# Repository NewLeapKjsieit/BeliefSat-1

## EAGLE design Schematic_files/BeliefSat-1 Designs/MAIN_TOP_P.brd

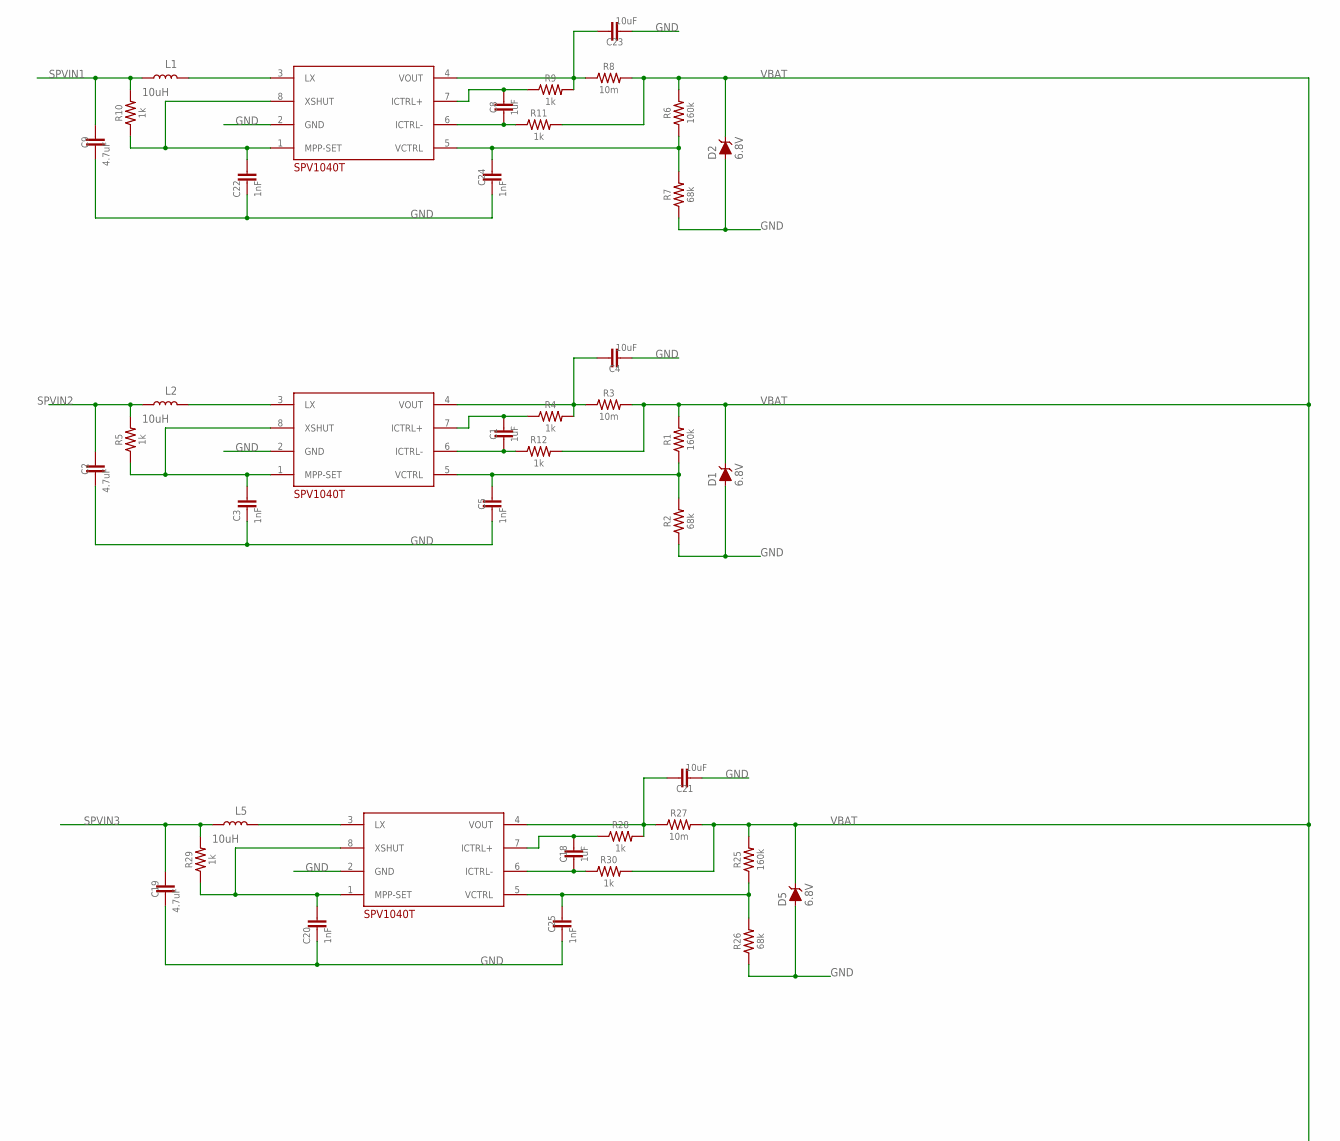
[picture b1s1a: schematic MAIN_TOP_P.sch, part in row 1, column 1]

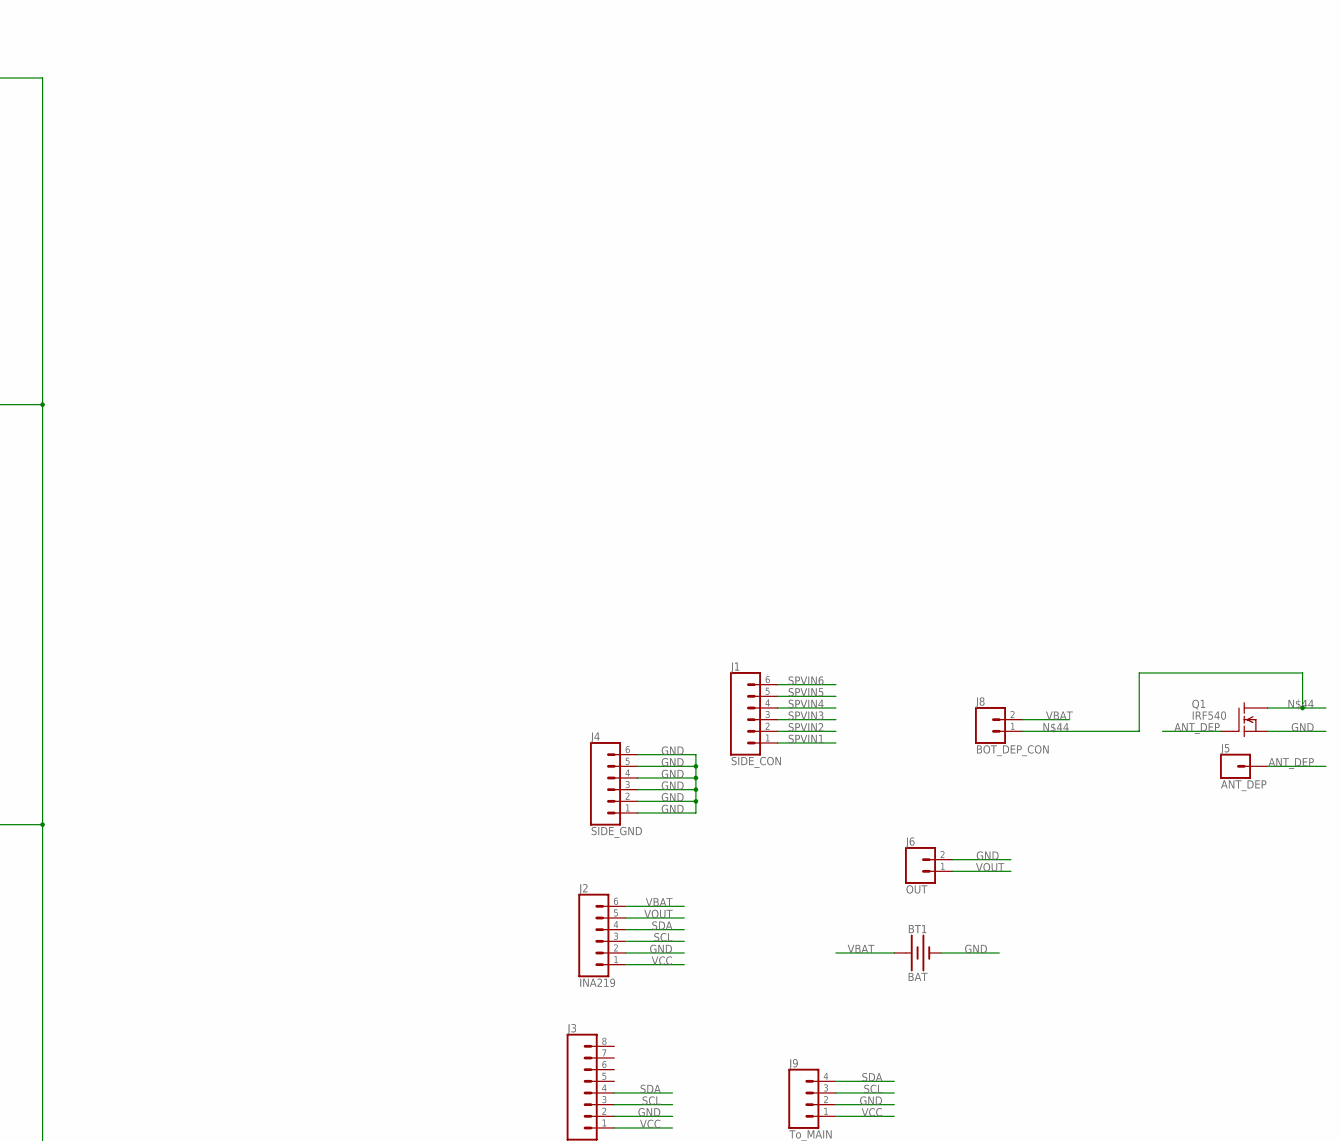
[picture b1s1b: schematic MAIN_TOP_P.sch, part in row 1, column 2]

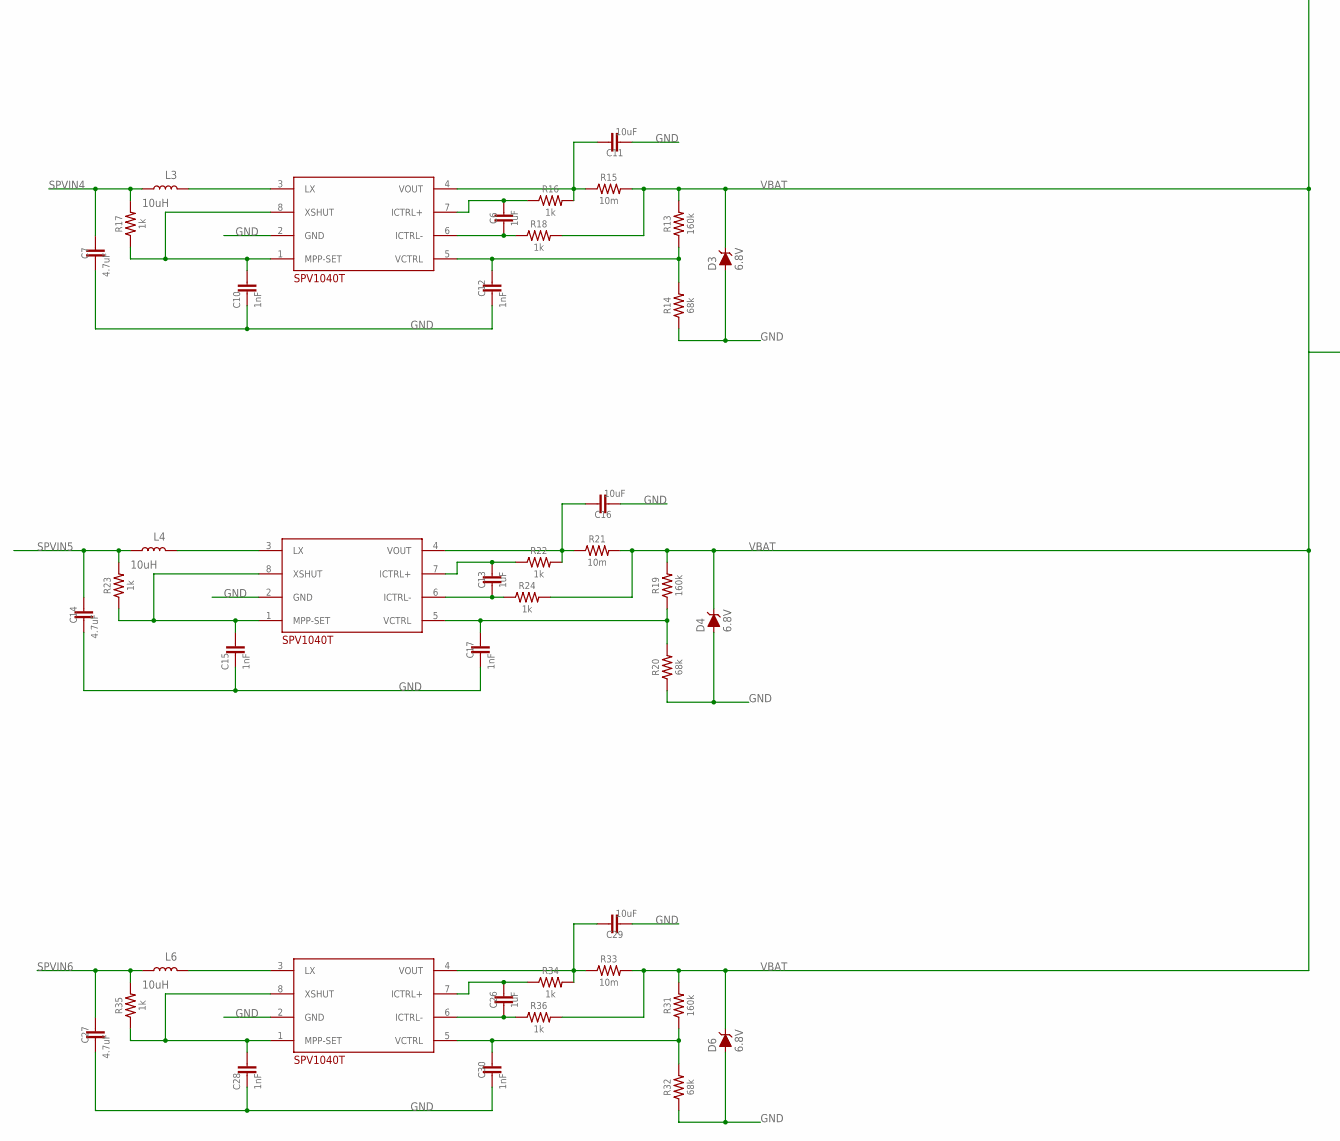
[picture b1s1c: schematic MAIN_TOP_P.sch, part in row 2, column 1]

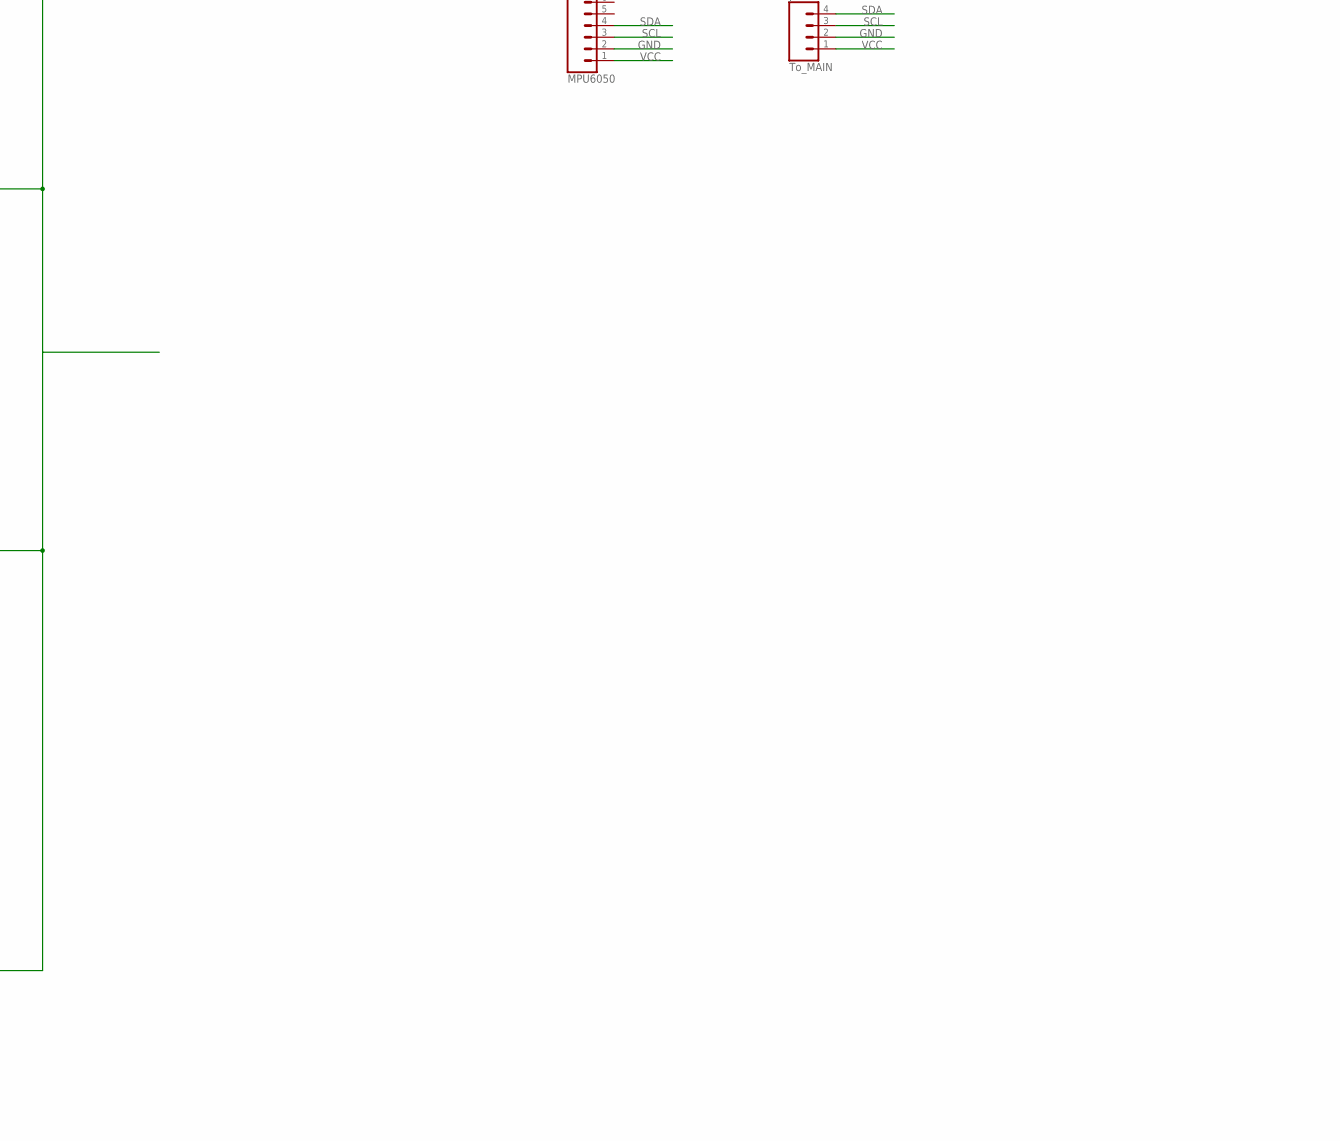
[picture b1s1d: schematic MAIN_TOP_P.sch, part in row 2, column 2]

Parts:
BT1: BAT; BATTERY_18650-HOLDER
C1, C6, C8, C13, C18, C26: 1uF; 0603
C2, C7, C9, C14, C19, C27: 4.7uF; 0603
C3, C5, C10, C12, C15, C17, C20, C22, C24, C25, C28, C30: 1nF; 0603
C4, C11, C16, C21, C23, C29: 10uF; 0603
D1, D2, D3, D4, D5, D6: 6.8V; SOD-323
J1: SIDE_CON; 1X06
J2: INA219; 1X06
J3: MPU6050; 1X08
J4: SIDE_GND; 1X06
J5: ANT_DEP; 1X01
J6: OUT; 1X02
J8: BOT_DEP_CON; 1X02
J9: To_MAIN; 1X04
L1, L2, L3, L4, L5, L6: 10uH; 0603
Q1: IRF540; TO220
R1, R6, R13, R19, R25, R31: 160k; RES_0603
R2, R7, R14, R20, R26, R32: 68k; RES_0603
R3, R8, R15, R21, R27, R33: 10m; RES_0603
R4, R5, R9, R10, R11, R12, R16, R17, R18, R22, R23, R24, R28, R29, R30, R34, R35, R36: 1k; RES_0603
SPV_1, SPV_2, SPV_3, SPV_4, SPV_5, SPV_6: SPV1040T_; SOP65P640X120-8N

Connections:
ANT_DEP: J5.1, Q1.1 (G)
GND: BT1.GND@1 (-), C2.2, C3.2, C4.2, C5.2, C7.2, C9.2, C10.2, C11.2, C12.2, C14.2, C15.2, C16.2, C17.2, C19.2, C20.2, C21.2, C22.2, C23.2, C24.2, C25.2, C27.2, C28.2, C29.2, C30.2, D1.A, D2.A, D3.A, D4.A, D5.A, D6.A, J2.2, J3.2, J4.1, J4.2, J4.3, J4.4, J4.5, J4.6, J6.2, J9.2, Q1.3 (S), R2.1, R7.1, R14.1, R20.1, R26.1, R32.1, SPV_1.2 (GND), SPV_2.2 (GND), SPV_3.2 (GND), SPV_4.2 (GND), SPV_5.2 (GND), SPV_6.2 (GND)
unnamed: L2.2, SPV_2.3 (LX)
unnamed: C3.1, R5.1, SPV_2.1 (MPP-SET), SPV_2.8 (XSHUT)
unnamed: C5.1, R1.1, R2.2, SPV_2.5 (VCTRL)
unnamed: C1.2, R12.1, SPV_2.6 (ICTRL-)
unnamed: L1.2, SPV_1.3 (LX)
unnamed: C1.1, R4.1, SPV_2.7 (ICTRL+)
unnamed: C4.1, R3.1, R4.2, SPV_2.4 (VOUT)
unnamed: L3.2, SPV_4.3 (LX)
unnamed: C10.1, R17.1, SPV_4.1 (MPP-SET), SPV_4.8 (XSHUT)
unnamed: C12.1, R13.1, R14.2, SPV_4.5 (VCTRL)
unnamed: C6.2, R18.1, SPV_4.6 (ICTRL-)
unnamed: C6.1, R16.1, SPV_4.7 (ICTRL+)
unnamed: C11.1, R15.1, R16.2, SPV_4.4 (VOUT)
unnamed: L4.2, SPV_5.3 (LX)
unnamed: C15.1, R23.1, SPV_5.1 (MPP-SET), SPV_5.8 (XSHUT)
unnamed: C17.1, R19.1, R20.2, SPV_5.5 (VCTRL)
unnamed: C13.2, R24.1, SPV_5.6 (ICTRL-)
unnamed: C13.1, R22.1, SPV_5.7 (ICTRL+)
unnamed: C16.1, R21.1, R22.2, SPV_5.4 (VOUT)
unnamed: L5.2, SPV_3.3 (LX)
unnamed: C20.1, R29.1, SPV_3.1 (MPP-SET), SPV_3.8 (XSHUT)
unnamed: C25.1, R25.1, R26.2, SPV_3.5 (VCTRL)
unnamed: C18.2, R30.1, SPV_3.6 (ICTRL-)
unnamed: C18.1, R28.1, SPV_3.7 (ICTRL+)
unnamed: C21.1, R27.1, R28.2, SPV_3.4 (VOUT)
unnamed: L6.2, SPV_6.3 (LX)
unnamed: C28.1, R35.1, SPV_6.1 (MPP-SET), SPV_6.8 (XSHUT)
unnamed: C30.1, R31.1, R32.2, SPV_6.5 (VCTRL)
unnamed: C26.2, R36.1, SPV_6.6 (ICTRL-)
unnamed: C26.1, R34.1, SPV_6.7 (ICTRL+)
unnamed: C22.1, R10.1, SPV_1.1 (MPP-SET), SPV_1.8 (XSHUT)
unnamed: C24.1, R6.1, R7.2, SPV_1.5 (VCTRL)
unnamed: C29.1, R33.1, R34.2, SPV_6.4 (VOUT)
unnamed: C8.2, R11.1, SPV_1.6 (ICTRL-)
unnamed: C8.1, R9.1, SPV_1.7 (ICTRL+)
unnamed: C23.1, R8.1, R9.2, SPV_1.4 (VOUT)
unnamed: J8.1, Q1.2 (D)
SCL: J2.3, J3.3, J9.3
SDA: J2.4, J3.4, J9.4
SPVIN1: C9.1, J1.1, L1.1, R10.2
SPVIN2: C2.1, J1.2, L2.1, R5.2
SPVIN3: C19.1, J1.3, L5.1, R29.2
SPVIN4: C7.1, J1.4, L3.1, R17.2
SPVIN5: C14.1, J1.5, L4.1, R23.2
SPVIN6: C27.1, J1.6, L6.1, R35.2
VBAT: BT1.PWR@1 (+), D1.C, D2.C, D3.C, D4.C, D5.C, D6.C, J2.6, J8.2, R1.2, R3.2, R6.2, R8.2, R11.2, R12.2, R13.2, R15.2, R18.2, R19.2, R21.2, R24.2, R25.2, R27.2, R30.2, R31.2, R33.2, R36.2
VCC: J2.1, J3.1, J9.1
VOUT: J2.5, J6.1

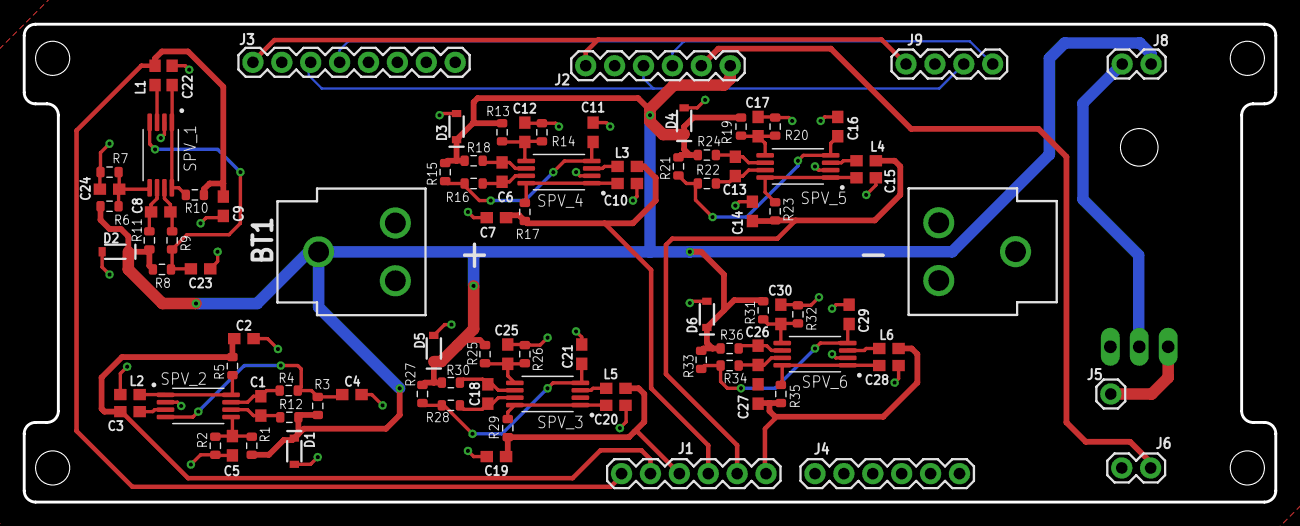
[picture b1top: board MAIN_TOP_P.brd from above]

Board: 2 copper layers, 110.0 x 42.0 mm, 94 parts (1 on the bottom side), 50 nets.

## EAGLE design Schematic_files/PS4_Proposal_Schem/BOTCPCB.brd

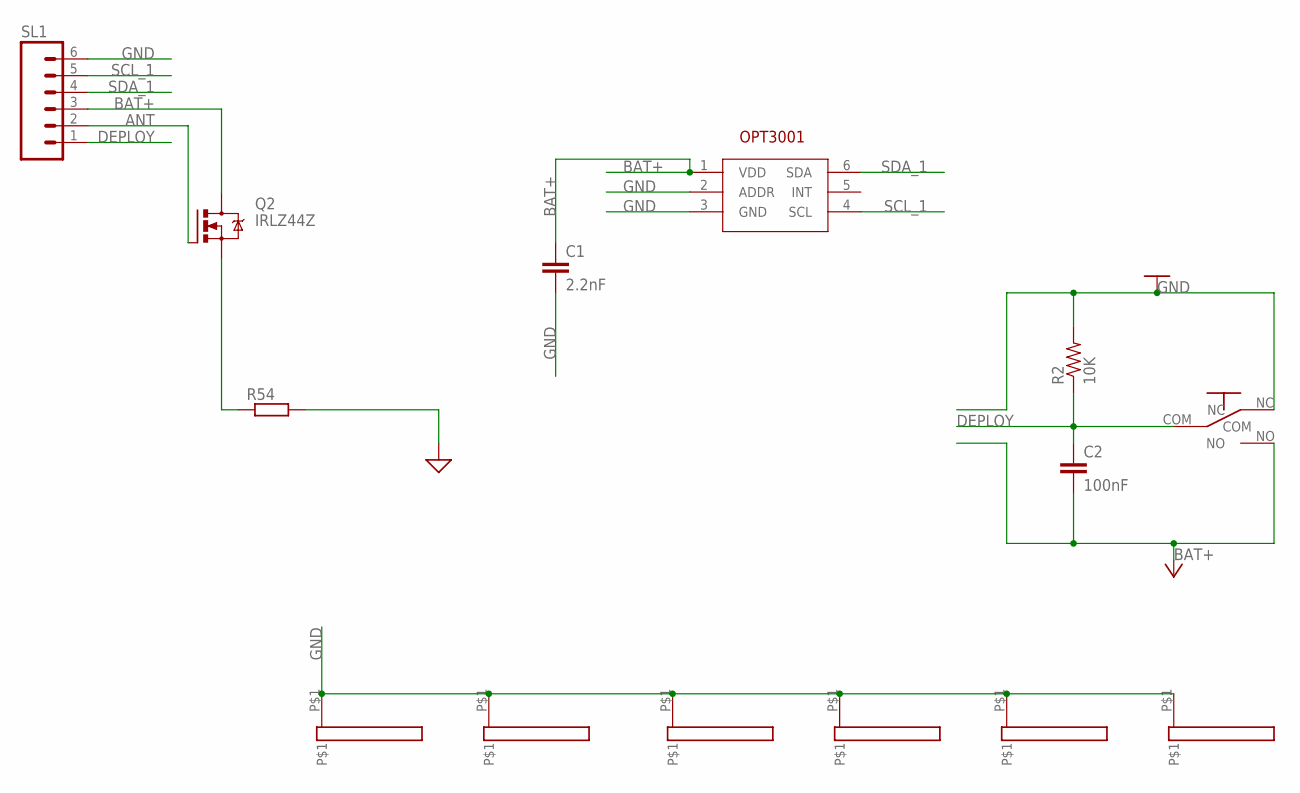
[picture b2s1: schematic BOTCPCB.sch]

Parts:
C1: 2.2nF; 0603
C2: 100nF; 0805
Q2: IRLZ44Z; TO220BH
R2: 10K; 0805
R54: R-EU_0204/2V; 0204V
SL1: M06; 06P
U1: SON65P200X200X65-7N
U$1, U$2, U$4, U$5, U$7, U$8: 16X2
U$6: OMRON-D2FA; OMRON-D2F-A

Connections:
ANT: Q2.G, SL1.2
BAT+: C1.1, C2.2, Q2.D, SL1.3, U1.1 (VDD), U$6.NO
DEPLOY: C2.1, R2.1, SL1.1, U$6.COM
GND: C1.2, R2.2, R54.2, SL1.6, U1.2 (ADDR), U1.3 (GND), U$1.P$1, U$2.P$1, U$4.P$1, U$5.P$1, U$6.NC, U$7.P$1, U$8.P$1
unnamed: Q2.S, R54.1
SCL_1: SL1.5, U1.4 (SCL)
SDA_1: SL1.4, U1.6 (SDA)

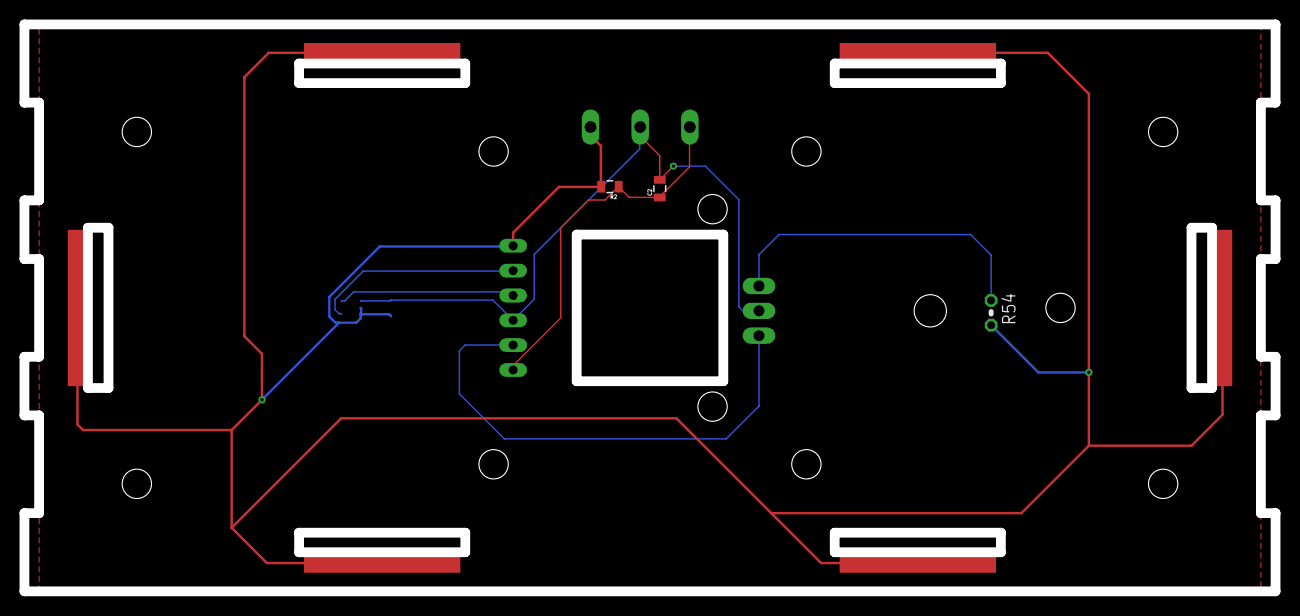
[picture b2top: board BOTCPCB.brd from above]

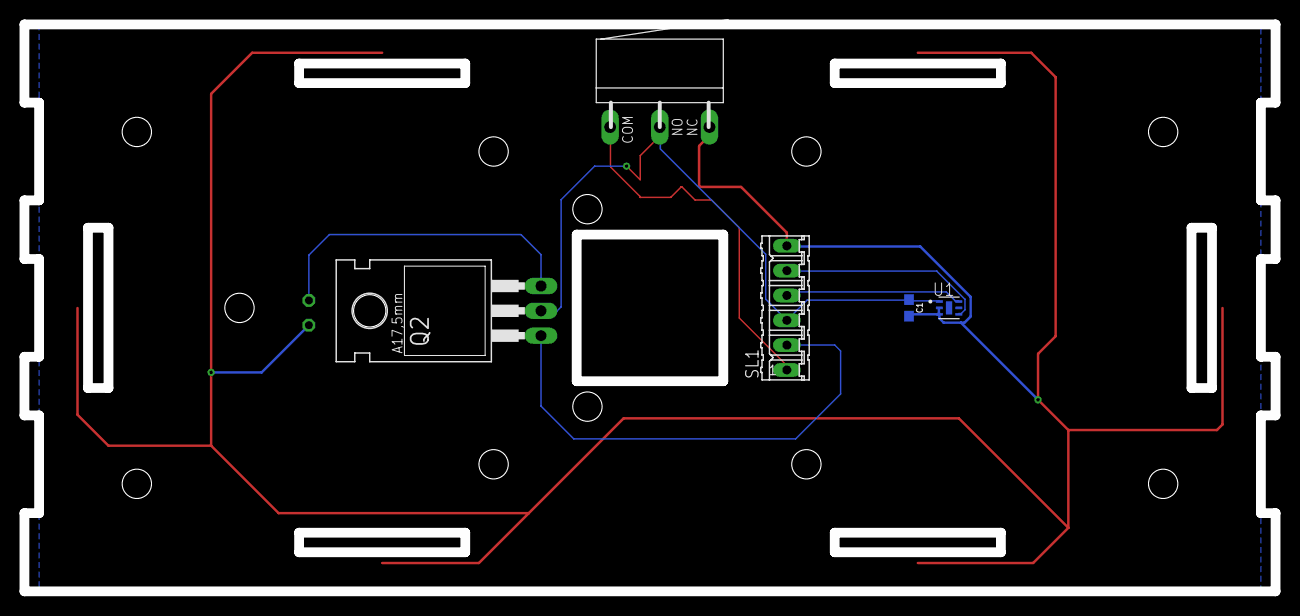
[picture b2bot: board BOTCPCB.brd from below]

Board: 2 copper layers, 128.0 x 58.0 mm, 14 parts (5 on the bottom side), 7 nets.

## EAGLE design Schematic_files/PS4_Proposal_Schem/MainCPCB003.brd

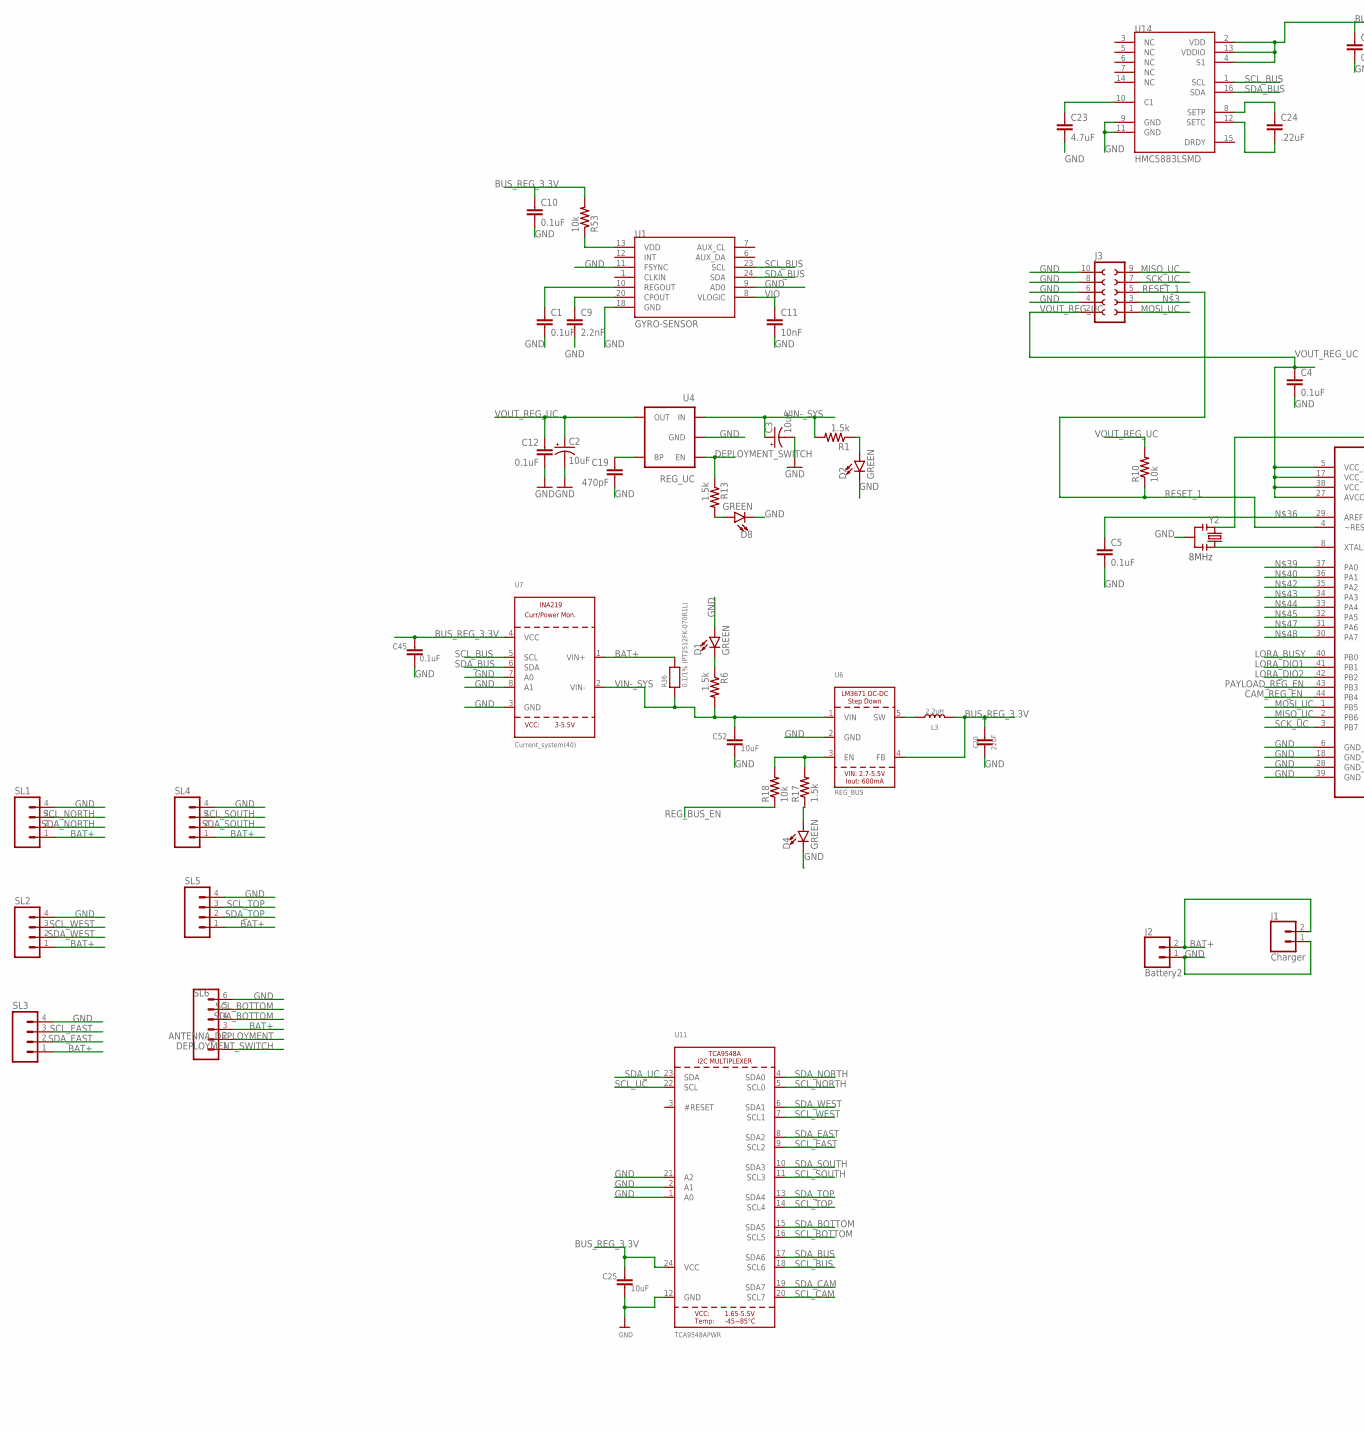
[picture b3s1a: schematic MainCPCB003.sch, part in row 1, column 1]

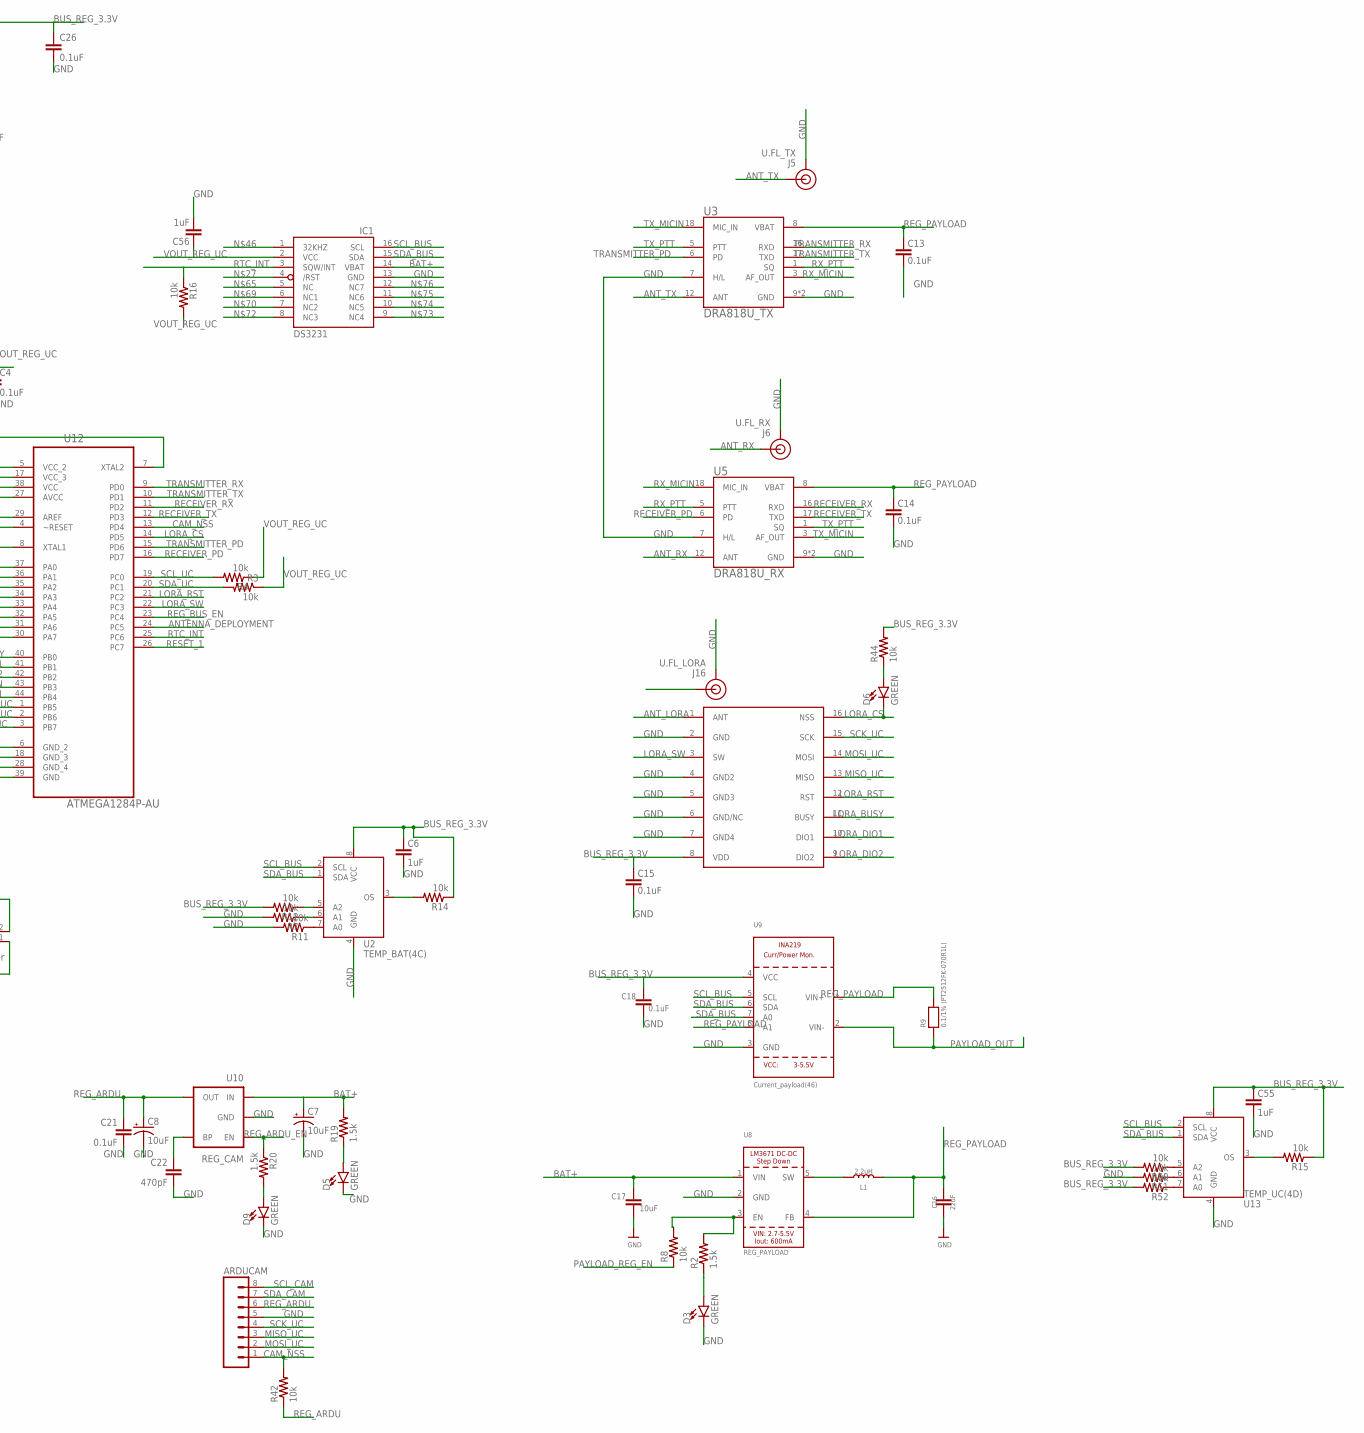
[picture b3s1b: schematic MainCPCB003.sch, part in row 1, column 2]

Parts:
ARDUCAM: M08; 08P
C1, C4, C5, C10, C12, C13, C14, C15, C21: 0.1uF; 0603-CAP
C2, C3, C7, C8: 10uF; 0603-POLAR
C6, C55, C56: 1uF; 0603-CAP
C9: 2.2nF; 0603-CAP
C11: 10nF; 0603-CAP
C16, C20: 22uF; 0603
C17, C25, C52: 10uF; 0603
C18, C26, C45: 0.1uF; 0603
C19, C22: 470pF; 0603-CAP
C23: 4.7uF; 0603
C24: .22uF; 0603
D1, D2, D3, D4, D5, D6, D8, D9: GREEN; LED-0603
IC1: DS3231/SO; SO16W
J1: Charger; 1X02
J2: Battery2; 1X02
J3: SOCKET-10V; S10V
J5: U.FL_TX; U.FL
J6: U.FL_RX; U.FL
J16: U.FL_LORA; U.FL
L1, L3: 2.2uH; 0603
R1, R2, R6, R13, R17, R19, R20: 1.5k; 0603-RES
R3, R4, R7, R11, R12, R14, R15, R16, R18, R42, R44, R50, R51, R52, R53: 10k; 0603-RES
R8, R10: 10k; 0402-RES
R9, R36: 0.1/1% (PT2512FK-070R1L); 2512
SL1, SL2, SL3, SL4, SL5: M04; 04P
SL6: M06; 06P
U1: GYRO-SENSOR; QFN-24-4MM2
U2: TEMP_BAT(4C); SOT505-1
U3: DRA818U_TX; DORJI_DRA818U
U4: REG_UC; SOT23-5
U5: DRA818U_RX; DORJI_DRA818U
U6: REG_BUS; SOT23-5
U7: Current_system(40); SOT23-8
U8: REG_PAYLOAD; SOT23-5
U9: Current_payload(46); SOT23-8
U10: REG_CAM; SOT23-5
U11: TCA9548APWR; TSSOP24
U12: ATMEGA1284P-AU; QFP80P1200X1200X120-44N
U13: TEMP_UC(4D); SOT505-1
U14: HMC5883LSMD; 16LPCC
U$1: DRF1268; RESCAV180P1570X1400X300-16
Y2: RESONATORSMD; RESONATOR-SMD

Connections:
ANTENNA_DEPLOYMENT: SL6.2, U12.24 (PC5)
ANT_LORA: J16.FEED (SIGNAL), U$1.1 (ANT)
ANT_RX: J6.FEED (SIGNAL), U5.12 (ANT)
ANT_TX: J5.FEED (SIGNAL), U3.12 (ANT)
BAT+: C7.+, C17.1, IC1.14 (VBAT), J1.2, J2.2, R19.2, R36.2, SL1.1, SL2.1, SL3.1, SL4.1, SL5.1, SL6.3, U7.1 (VIN+), U8.1 (VIN), U10.1 (IN)
BUS_REG_3.3V: C6.2, C10.1, C15.2, C18.1, C20.1, C25.1, C26.1, C45.1, C55.2, L3.2, R12.2, R14.1, R15.1, R44.2, R50.2, R52.2, R53.2, U2.8 (VCC), U6.4 (FB), U7.4 (VCC), U9.4 (VCC), U11.24 (VCC), U13.8 (VCC), U14.2 (VDD), U14.4 (S1), U14.13 (VDDIO), U$1.8 (VDD)
CAM_NSS: ARDUCAM.1, R42.2, U12.13 (PD4)
CAM_REG_EN: U12.44 (PB4)
DEPLOYMENT_SWITCH: R13.1, SL6.1, U4.3 (EN)
GND: ARDUCAM.5, C1.2, C2.-, C3.-, C4.2, C5.2, C6.1, C7.-, C8.-, C9.2, C10.2, C11.2, C12.2, C13.1, C14.1, C15.1, C16.2, C17.2, C18.2, C19.2, C20.2, C21.2, C22.2, C23.2, C25.2, C26.2, C45.2, C52.2, C55.1, C56.1, D1.A, D2.C, D3.C, D4.C, D5.C, D8.C, D9.C, IC1.13 (GND), J1.1, J2.1, J3.4, J3.6, J3.8, J3.10, J5.1 (GND), J5.2 (GND), J6.1 (GND), J6.2 (GND), J16.1 (GND), J16.2 (GND), R7.2, R11.2, R51.2, SL1.4, SL2.4, SL3.4, SL4.4, SL5.4, SL6.6, U1.9 (AD0), U1.11 (FSYNC), U1.18 (GND), U2.4 (GND), U3.7 (H/L), U3.9 (GND), U3.10 (GND), U4.2 (GND), U5.7 (H/L), U5.9 (GND), U5.10 (GND), U6.2 (GND), U7.3 (GND), U7.7 (A0), U7.8 (A1), U8.2 (GND), U9.3 (GND), U10.2 (GND), U11.1 (A0), U11.2 (A1), U11.12 (GND), U11.21 (A2), U12.6 (GND_2), U12.18 (GND_3), U12.28 (GND_4), U12.39 (GND), U13.4 (GND), U14.9 (GND), U14.11 (GND), U$1.2 (GND), U$1.4 (GND2), U$1.5 (GND3), U$1.6 (GND/NC), U$1.7 (GND4), Y2.2
LORA_BUSY: U12.40 (PB0), U$1.11 (BUSY)
LORA_CS: D6.C, U12.14 (PD5), U$1.16 (NSS)
LORA_DIO1: U12.41 (PB1), U$1.10 (DIO1)
LORA_DIO2: U12.42 (PB2), U$1.9 (DIO2)
LORA_RST: U12.21 (PC2), U$1.12 (RST)
LORA_SW: U12.22 (PC3), U$1.3 (SW)
MISO_UC: ARDUCAM.3, J3.9, U12.2 (PB6), U$1.13 (MISO)
MOSI_UC: ARDUCAM.2, J3.1, U12.1 (PB5), U$1.14 (MOSI)
unnamed: D5.A, R19.1
unnamed: D8.A, R13.2
unnamed: R7.1, U2.6 (A1)
unnamed: D4.A, R17.1
unnamed: D3.A, R2.1
unnamed: D2.A, R1.1
unnamed: R17.2, R18.2, U6.3 (EN)
unnamed: R2.2, R8.2, U8.3 (EN)
unnamed: D1.C, R6.1
unnamed: D6.A, R44.1
unnamed: L1.1, U8.5 (SW)
unnamed: C22.1, U10.4 (BP)
unnamed: U12.7 (XTAL2), Y2.1
unnamed: D9.A, R20.2
unnamed: C24.1, U14.8 (SETP)
unnamed: C24.2, U14.12 (SETC)
unnamed: C23.1, U14.10 (C1)
unnamed: L3.1, U6.5 (SW)
unnamed: C19.1, U4.4 (BP)
unnamed: C9.1, U1.20 (CPOUT)
unnamed: C1.1, U1.10 (REGOUT)
unnamed: U12.8 (XTAL1), Y2.3
unnamed: R53.1, U1.13 (VDD)
unnamed: R12.1, U2.5 (A2)
unnamed: C5.1, U12.29 (AREF)
unnamed: R11.1, U2.7 (A0)
unnamed: R14.2, U2.3 (OS)
unnamed: R50.1, U13.5 (A2)
unnamed: R51.1, U13.6 (A1)
unnamed: R52.1, U13.7 (A0)
unnamed: R15.2, U13.3 (OS)
PAYLOAD_OUT: R9.1, U9.2 (VIN-)
PAYLOAD_REG_EN: R8.1, U12.43 (PB3)
RECEIVER_PD: U5.6 (PD), U12.16 (PD7)
RECEIVER_RX: U5.16 (RXD), U12.11 (PD2)
RECEIVER_TX: U5.17 (TXD), U12.12 (PD3)
REG_ARDU: ARDUCAM.6, C8.+, C21.1, R42.1, U10.5 (OUT)
REG_ARDU_EN: R20.1, U10.3 (EN)
REG_BUS_EN: R18.1, U12.23 (PC4)
REG_PAYLOAD: C13.2, C14.2, C16.1, L1.2, R9.2, U3.8 (VBAT), U5.8 (VBAT), U8.4 (FB), U9.1 (VIN+), U9.8 (A1)
RESET_1: J3.5, R10.1, U12.4 (~RESET), U12.26 (PC7)
RTC_INT: IC1.3 (SQW/INT), R16.1, U12.25 (PC6)
RX_MICIN: U3.3 (AF_OUT), U5.18 (MIC_IN)
RX_PTT: U3.1 (SQ), U5.5 (PTT)
SCK_UC: ARDUCAM.4, J3.7, U12.3 (PB7), U$1.15 (SCK)
SCL_BOTTOM: SL6.5, U11.16 (SCL5)
SCL_BUS: IC1.16 (SCL), U1.23 (SCL), U2.2 (SCL), U7.5 (SCL), U9.5 (SCL), U11.18 (SCL6), U13.2 (SCL), U14.1 (SCL)
SCL_CAM: ARDUCAM.8, U11.20 (SCL7)
SCL_EAST: SL3.3, U11.9 (SCL2)
SCL_NORTH: SL1.3, U11.5 (SCL0)
SCL_SOUTH: SL4.3, U11.11 (SCL3)
SCL_TOP: SL5.3, U11.14 (SCL4)
SCL_UC: R4.2, U11.22 (SCL), U12.19 (PC0)
SCL_WEST: SL2.3, U11.7 (SCL1)
SDA_BOTTOM: SL6.4, U11.15 (SDA5)
SDA_BUS: IC1.15 (SDA), U1.24 (SDA), U2.1 (SDA), U7.6 (SDA), U9.6 (SDA), U9.7 (A0), U11.17 (SDA6), U13.1 (SDA), U14.16 (SDA)
SDA_CAM: ARDUCAM.7, U11.19 (SDA7)
SDA_EAST: SL3.2, U11.8 (SDA2)
SDA_NORTH: SL1.2, U11.4 (SDA0)
SDA_SOUTH: SL4.2, U11.10 (SDA3)
SDA_TOP: SL5.2, U11.13 (SDA4)
SDA_UC: R3.2, U11.23 (SDA), U12.20 (PC1)
SDA_WEST: SL2.2, U11.6 (SDA1)
TRANSMITTER_PD: U3.6 (PD), U12.15 (PD6)
TRANSMITTER_RX: U3.16 (RXD), U12.9 (PD0)
TRANSMITTER_TX: U3.17 (TXD), U12.10 (PD1)
TX_MICIN: U3.18 (MIC_IN), U5.3 (AF_OUT)
TX_PTT: U3.5 (PTT), U5.1 (SQ)
VIN-_SYS: C3.+, C52.1, R1.2, R6.2, R36.1, U4.1 (IN), U6.1 (VIN), U7.2 (VIN-)
VIO: C11.1, U1.8 (VLOGIC)
VOUT_REG_UC: C2.+, C4.1, C12.1, C56.2, IC1.2 (VCC), J3.2, R3.1, R4.1, R10.2, R16.2, U4.5 (OUT), U12.5 (VCC_2), U12.17 (VCC_3), U12.27 (AVCC), U12.38 (VCC)

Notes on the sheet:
8MHz

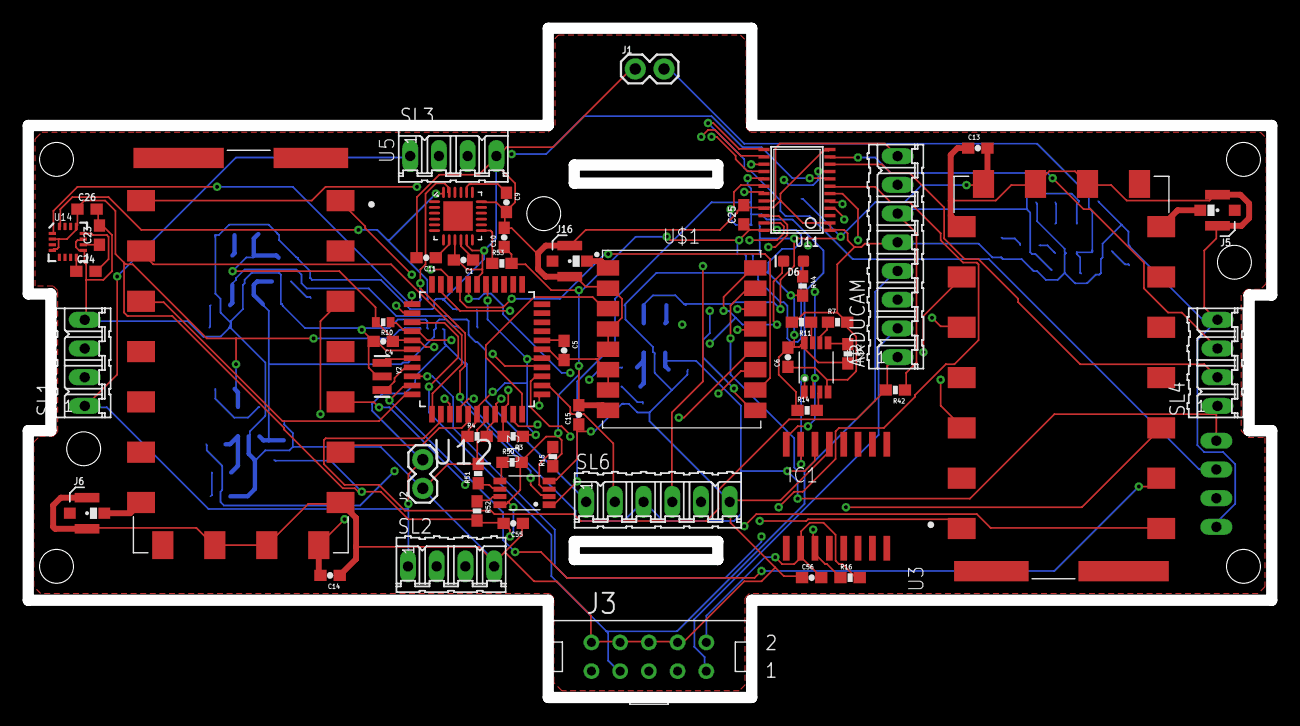
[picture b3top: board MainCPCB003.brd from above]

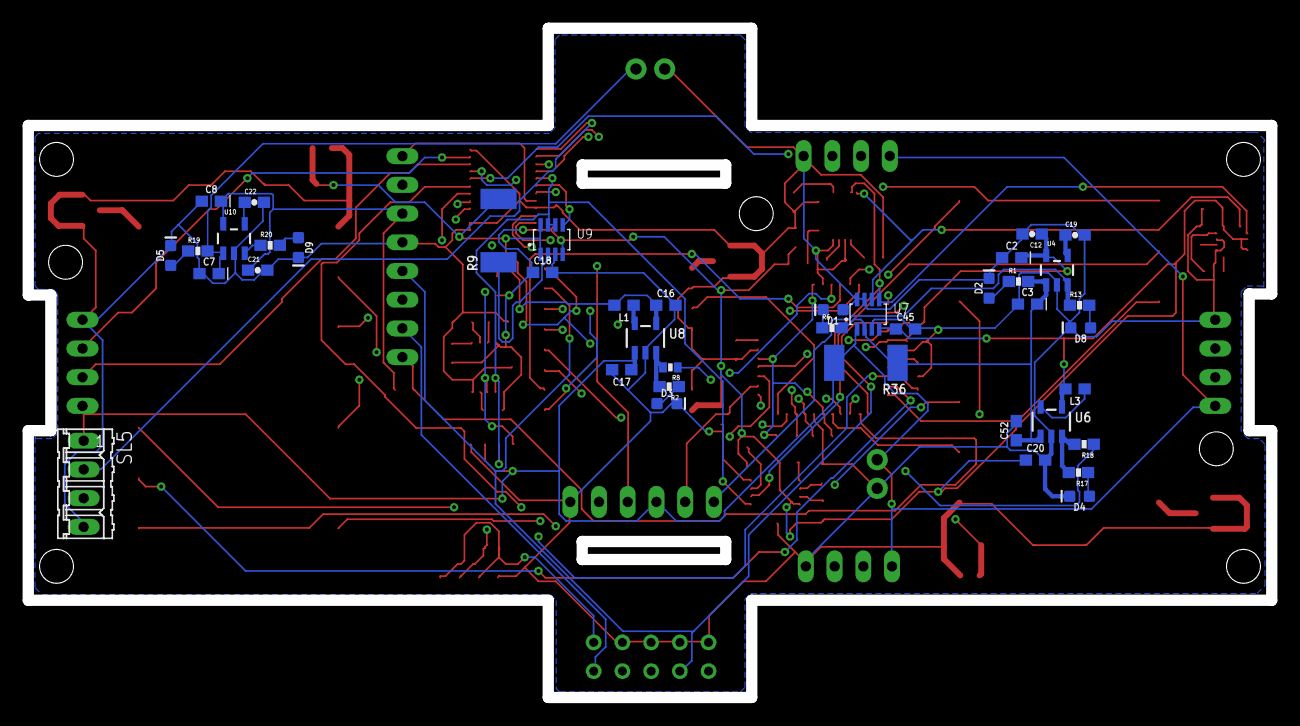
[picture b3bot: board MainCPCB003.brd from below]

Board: 4 copper layers, 110.0 x 59.2 mm, 96 parts (41 on the bottom side), 88 nets.

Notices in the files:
parts and their libraries:
SparkFun-Capacitors: Licensing: Creative Commons ShareAlike 4.0 International - https://creativecommons.org/licenses/by-sa/4.0
microbuilder: This work is placed in the public domain, and may be freely used for commercial and non-commercial work with the following conditions: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
